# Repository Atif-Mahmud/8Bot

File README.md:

<h1 align="center">
    <br>
    
    <br>
    8Bot
    <br>
</h1>

<h4 align="center">Autonomous Pool Robot using Computer Vision</h4>

<h5 align="center">By: Atif Mahmud and Ethan Guo</h5>

<p align="center">

</p>

<p align="center">
    <a href="#procedures">Background and Motivation</a> •
    <a href="#procedures">Procedures</a> •
    <a href="#related-works">Related Works</a> •
    <a href="#learning-goals">Learning Goals</a> •
    <a href="#engineering-goals">Engineering Goals</a> •
    <a href="#license">License</a>
</p>

# Background and Motivation

# Procedures
## Dependencies
### Python Libraries
The projects primary language is python. Input parsing, computer vision, and
pathfinding are executed by python clients. The
[OpenCV-Python](https://docs.opencv.org/3.4.3/index.html) wrapper is used along
with [Numpy](http://www.numpy.org/) to do the various computer vision and
matrix operations this project employs.

#### Install Python-OpenCV
```shell
sudo apt-get install python-opencv
```

#### Install Pip
```shell
sudo apt-get install python-pip
```

#### Install Numpy
```shell
pip install numpy
```

### MQTT Broker
This project relies on low latency publisher/subscriber based data transfer. To
do this we employ MQTT. MQTT (Message Queuing Telemetry Transport) is an ISO
Standard messaging protocol commonly used in IOT applications. The one caveat
is that its publish/subscriber message pattern requires a persistent broker.
For the purposes of this project we employ the open source MQTT broker [Eclipse
Mosquitto](https://mosquitto.org).

#### Install Broker (Ubuntu)

(Ubuntu 12^)
```shell
sudo apt install mosquitto
```

(Older versions of Ubuntu)
```shell
sudo apt-add-repository ppa:mosquitto-dev/mosquitto-ppa
sudo apt-get update
```

#### Install Python MQTT Client Library
```shell
pip install paho-mqtt
```

# Learning Goals
- [ ] Continuous Integration
- [x] MQTT Protocol

# Engineering Goals
- [ ] Fast robot messaging infrastructure
- [ ] Robust object classification
- [ ] Robust environment description
- [ ] Robust localization

# Related Works

# License

GNU GENERAL PUBLIC LICENSE
Version 3, 29 June 2007

Refer to LICENSE.txt for full details

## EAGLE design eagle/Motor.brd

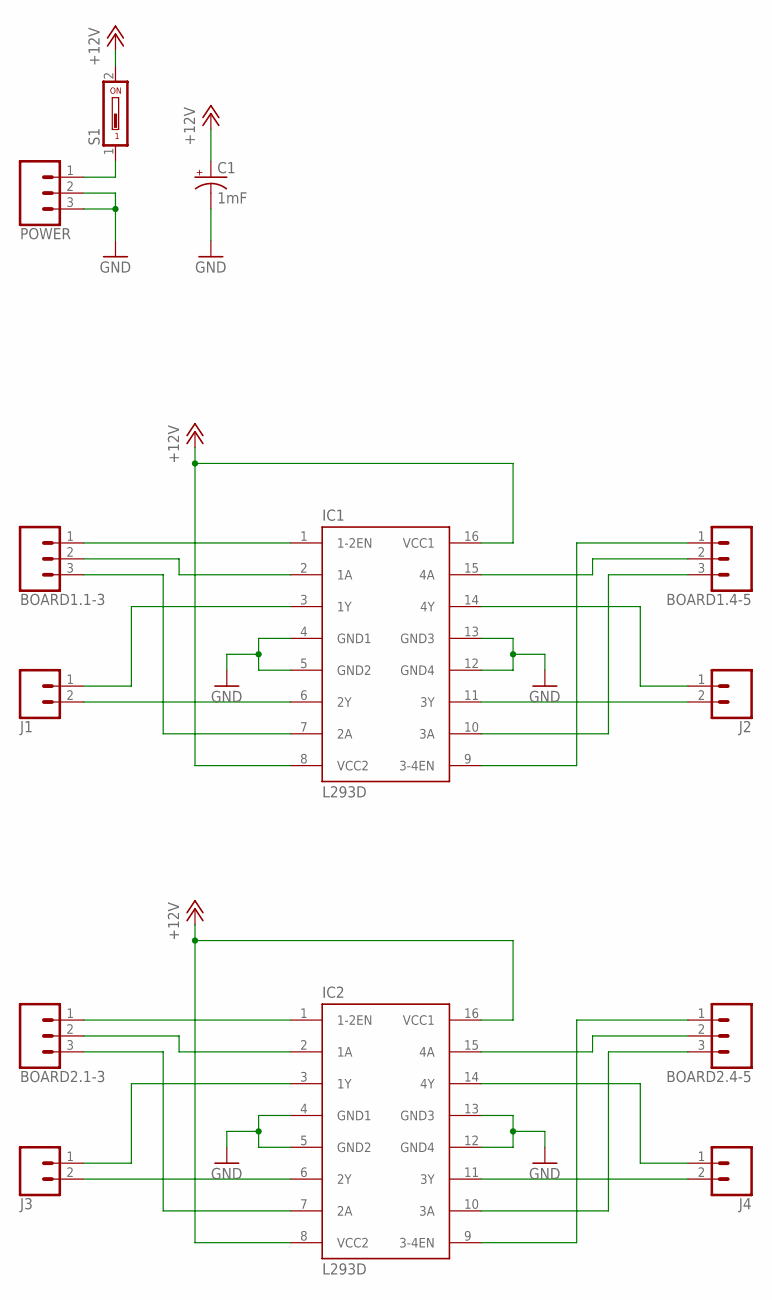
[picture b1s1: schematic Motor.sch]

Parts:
BOARD1.1-3, BOARD1.4-5, BOARD2.1-3, BOARD2.4-5: CONN_03; 1X03
C1: 1mF; CPOL-RADIAL-5MM-10MM
IC1, IC2: L293D; DIL16
J1, J2, J3, J4: CONN_02; 1X02
POWER: CONN_03; 1X03
S1: DS01; DS-01

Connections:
+9V: C1.+, IC1.8 (VCC2), IC1.16 (VCC1), IC2.8 (VCC2), IC2.16 (VCC1), S1.2
EN1: BOARD1.1-3.1, IC1.1 (1-2EN)
EN2: BOARD2.1-3.1, IC2.1 (1-2EN)
GND: C1.-, IC1.4 (GND1), IC1.5 (GND2), IC1.12 (GND4), IC1.13 (GND3), IC2.4 (GND1), IC2.5 (GND2), IC2.12 (GND4), IC2.13 (GND3), POWER.2, POWER.3
unnamed: IC1.3 (1Y), J1.1
unnamed: IC1.6 (2Y), J1.2
unnamed: IC1.14 (4Y), J2.1
unnamed: IC1.11 (3Y), J2.2
unnamed: BOARD1.1-3.2, IC1.2 (1A)
unnamed: BOARD1.1-3.3, IC1.7 (2A)
unnamed: BOARD1.4-5.3, IC1.10 (3A)
unnamed: BOARD1.4-5.2, IC1.15 (4A)
unnamed: IC2.3 (1Y), J3.1
unnamed: IC2.6 (2Y), J3.2
unnamed: IC2.14 (4Y), J4.1
unnamed: IC2.11 (3Y), J4.2
unnamed: BOARD2.1-3.2, IC2.2 (1A)
unnamed: BOARD2.1-3.3, IC2.7 (2A)
unnamed: BOARD2.4-5.1, IC2.9 (3-4EN)
unnamed: BOARD1.4-5.1, IC1.9 (3-4EN)
unnamed: BOARD2.4-5.3, IC2.10 (3A)
unnamed: BOARD2.4-5.2, IC2.15 (4A)
unnamed: POWER.1, S1.1

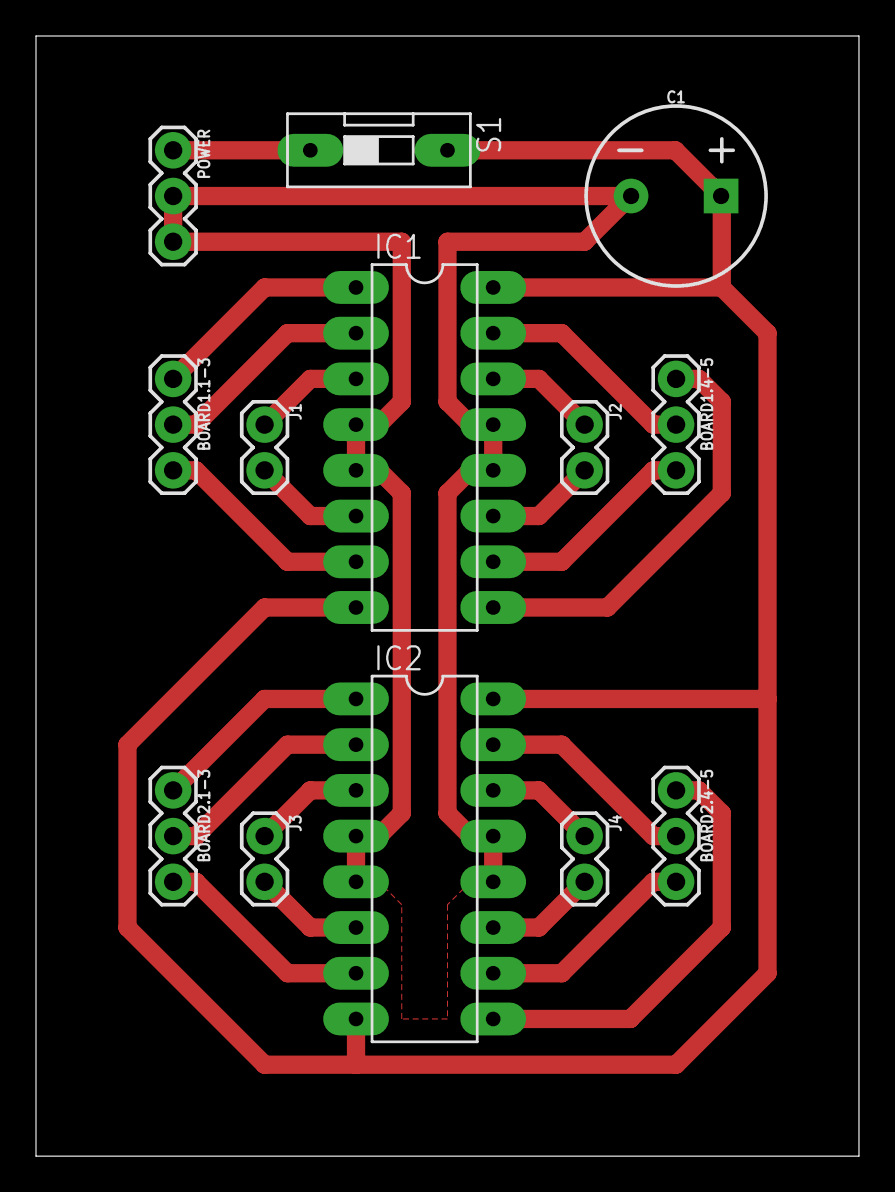
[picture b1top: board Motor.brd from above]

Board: 2 copper layers, 45.7 x 62.2 mm, 13 parts (0 on the bottom side), 23 nets.

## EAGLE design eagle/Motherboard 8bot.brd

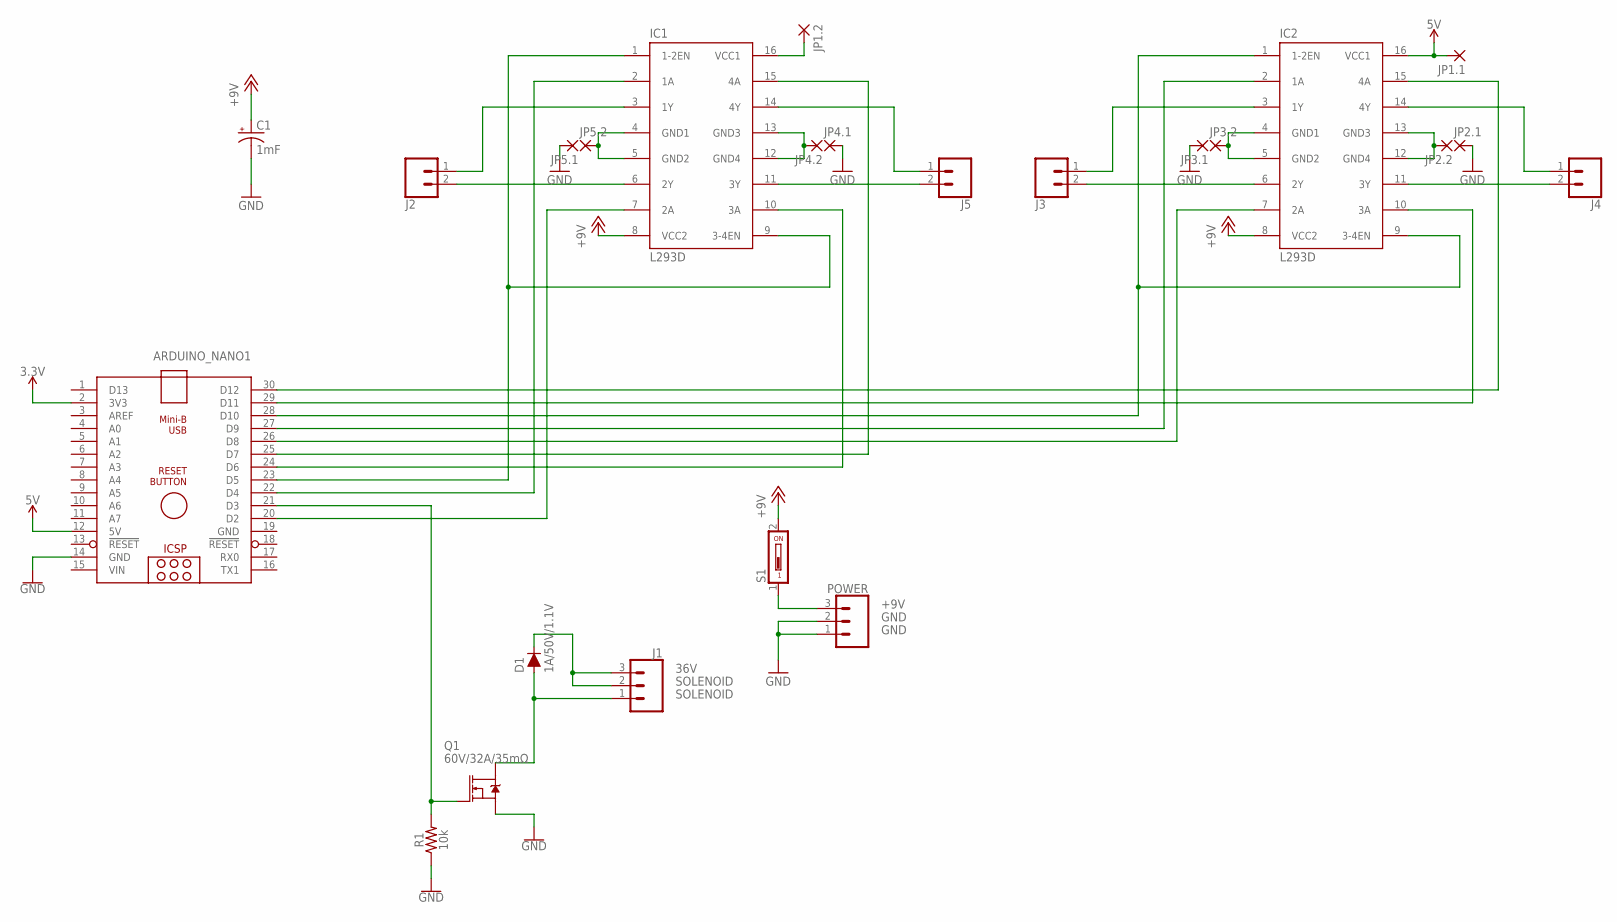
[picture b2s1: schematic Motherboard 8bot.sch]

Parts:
ARDUINO_NANO1: ARDUINO_NANO
C1: 1mF; CPOL-RADIAL-5MM-10MM
D1: 1A/50V/1.1V; DIODE-1N4001
IC1, IC2: L293D; DIL16
J1: CONN_03-SCREW-5MM; SCREWTERMINAL-5MM-3
J2, J3, J4, J5: CONN_02; 1X02
JP1.1, JP1.2, JP2.1, JP2.2, JP3.1, JP3.2, JP4.1, JP4.2, JP5.1, JP5.2: 1,6/0,8
POWER: CONN_03-SCREW-5MM; SCREWTERMINAL-5MM-3
Q1: 60V/32A/35mΩ; TO220V
R1: 10k; AXIAL-0.3
S1: DS01; DS-01

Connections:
3.3V: ARDUINO_NANO1.2 (3V3)
5V: ARDUINO_NANO1.12 (5V), IC2.16 (VCC1), JP1.1.1
36V: D1.C, J1.2, J1.3
+9V: C1.+, IC1.8 (VCC2), IC2.8 (VCC2), S1.2
EN1: ARDUINO_NANO1.23 (D5), IC1.1 (1-2EN), IC1.9 (3-4EN)
EN2: ARDUINO_NANO1.28 (D10), IC2.1 (1-2EN), IC2.9 (3-4EN)
GND: ARDUINO_NANO1.14 (GND), ARDUINO_NANO1.19 (GND), C1.-, JP2.1.1, JP3.1.1, JP4.1.1, JP5.1.1, POWER.1, POWER.2, Q1.3 (S), R1.P$1 (1)
unnamed: ARDUINO_NANO1.21 (D3), Q1.1 (G), R1.P$2 (2)
unnamed: IC1.3 (1Y), J2.1
unnamed: IC1.6 (2Y), J2.2
unnamed: IC1.14 (4Y), J5.1
unnamed: IC1.11 (3Y), J5.2
unnamed: ARDUINO_NANO1.20 (D2), IC1.7 (2A)
unnamed: ARDUINO_NANO1.22 (D4), IC1.2 (1A)
unnamed: ARDUINO_NANO1.24 (D6), IC1.10 (3A)
unnamed: IC2.3 (1Y), J3.1
unnamed: IC2.6 (2Y), J3.2
unnamed: IC2.14 (4Y), J4.1
unnamed: IC2.11 (3Y), J4.2
unnamed: IC1.16 (VCC1), JP1.2.1
unnamed: ARDUINO_NANO1.27 (D9), IC2.2 (1A)
unnamed: ARDUINO_NANO1.25 (D7), IC1.15 (4A)
unnamed: ARDUINO_NANO1.29 (D11), IC2.10 (3A)
unnamed: ARDUINO_NANO1.26 (D8), IC2.7 (2A)
unnamed: ARDUINO_NANO1.30 (D12), IC2.15 (4A)
unnamed: IC1.4 (GND1), IC1.5 (GND2), JP5.2.1
unnamed: POWER.3, S1.1
unnamed: IC1.12 (GND4), IC1.13 (GND3), JP4.2.1
unnamed: IC2.4 (GND1), IC2.5 (GND2), JP3.2.1
unnamed: IC2.12 (GND4), IC2.13 (GND3), JP2.2.1
SOLENOID: D1.A, J1.1, Q1.2 (D)
VIN: ARDUINO_NANO1.15 (VIN)

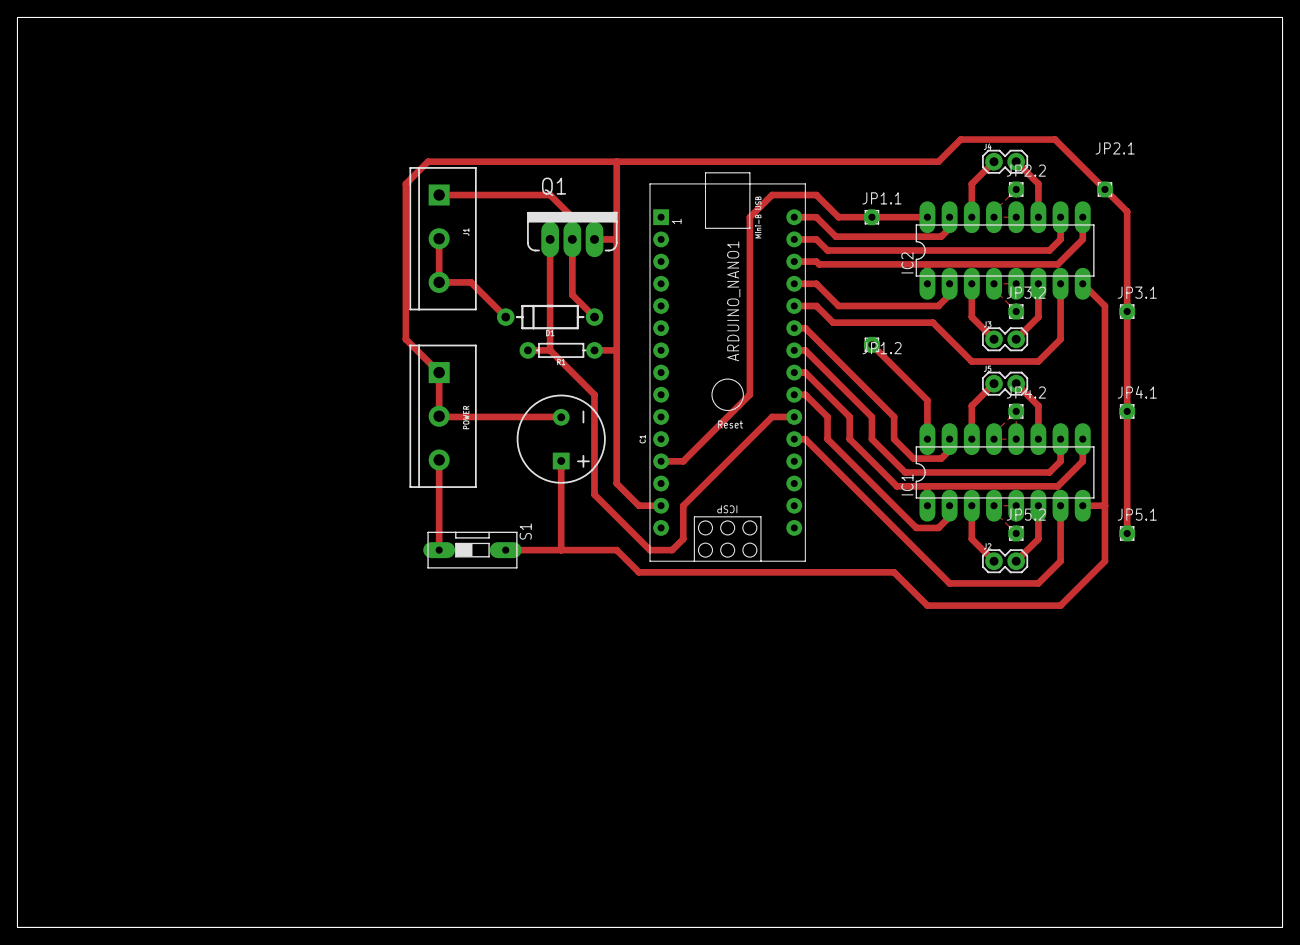
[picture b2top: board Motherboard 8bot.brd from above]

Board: 2 copper layers, 144.8 x 104.1 mm, 24 parts (0 on the bottom side), 30 nets.

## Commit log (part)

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2018-10-06 ✨ Add empty README file
2018-10-11 Make doc folder
2018-10-11 Compile proposal to pdf
2018-10-25 Add .gitignore
2018-10-25 Add bash script to initialize MQQT Broker
    References: #1
2018-10-25 ignore continuous integration temporarily
2018-10-25 Implement Master Controller general integration
    References: #4
2018-10-25 Implement Computer Vision integrations
    References: #2
2018-10-25 Remove debugging subscription
    Add error handling and logic to on_message()
    References: #4
2018-10-25 Add trivial ui integration
    References: #4
2018-10-30 Install packages
    References: #5
2018-10-30 Bootstrap Angular App with E2E testing
    References: #5
2018-11-01 Add continuous integration using .gitlab-ci.yml
    References: #5
2018-11-21 Design perspective transform class
    References #12
2018-11-21 Implement fourCorners method
    References: #12
2018-11-21 Add solenoid_test and (test) 8bot firmware
2018-11-21 Rename arduino/8bot/8bot.ino -> arduino/eightbot/eightbot.ino
2018-11-22 Create several ComputerVision utilities
    References #12
2018-11-22 Fixed taking commands, add debug stuff (LED and Serial echo)
2018-11-22 Implement calibrate class
    References: #13
2018-11-22 Rename cv_publisher.py to image_publisher.py
2018-11-22 Add keyboard_control.py
2018-11-22 Add debugging redundancies
2018-11-22 Computer Vision Demo V1
    References: #18
2018-11-22 Fix: Turn off DEBUG_ECHO Serial echo flag
2018-11-22 Improve calibration with contours
    References: #19
2018-11-22 Update MQTT publisher for CVNode
    References: #20
2019-09-24 Add gif to README.md
2019-11-01 Bump handlebars from 4.0.12 to 4.5.1 in /ui_node/eightbot
    Bumps [handlebars](https://github.com/wycats/handlebars.js) from 4.0.12 to 4.5.1.
    - [Release notes](https://github.com/wycats/handlebars.js/releases)
    - [Changelog](https://github.com/wycats/handlebars.js/blob/v4.5.1/release-notes.md)
    - [Commits](https://github.com/wycats/handlebars.js/compare/v4.0.12...v4.5.1)
2020-04-06 Bump acorn from 5.7.3 to 5.7.4 in /ui_node/eightbot
    Bumps [acorn](https://github.com/acornjs/acorn) from 5.7.3 to 5.7.4.
    - [Release notes](https://github.com/acornjs/acorn/releases)
    - [Commits](https://github.com/acornjs/acorn/compare/5.7.3...5.7.4)
2020-04-16 Bump https-proxy-agent from 2.2.1 to 2.2.4 in /ui_node/eightbot
    Bumps [https-proxy-agent](https://github.com/TooTallNate/node-https-proxy-agent) from 2.2.1 to 2.2.4.
    - [Release notes](https://github.com/TooTallNate/node-https-proxy-agent/releases)
    - [Commits](https://github.com/TooTallNate/node-https-proxy-agent/compare/2.2.1...2.2.4)
2020-07-31 Bump elliptic from 6.4.1 to 6.5.3 in /ui_node/eightbot
    Bumps [elliptic](https://github.com/indutny/elliptic) from 6.4.1 to 6.5.3.
    - [Release notes](https://github.com/indutny/elliptic/releases)
    - [Commits](https://github.com/indutny/elliptic/compare/v6.4.1...v6.5.3)
2020-09-04 Bump lodash.mergewith from 4.6.1 to 4.6.2 in /ui_node/eightbot
    Bumps [lodash.mergewith](https://github.com/lodash/lodash) from 4.6.1 to 4.6.2.
    - [Release notes](https://github.com/lodash/lodash/releases)
    - [Commits](https://github.com/lodash/lodash/commits)
2020-09-10 Bump http-proxy from 1.17.0 to 1.18.1 in /ui_node/eightbot
    Bumps [http-proxy](https://github.com/http-party/node-http-proxy) from 1.17.0 to 1.18.1.
    - [Release notes](https://github.com/http-party/node-http-proxy/releases)
    - [Changelog](https://github.com/http-party/node-http-proxy/blob/master/CHANGELOG.md)
    - [Commits](https://github.com/http-party/node-http-proxy/compare/1.17.0...1.18.1)
2020-12-11 Bump ini from 1.3.5 to 1.3.7 in /ui_node/eightbot
    Bumps [ini](https://github.com/isaacs/ini) from 1.3.5 to 1.3.7.
    - [Release notes](https://github.com/isaacs/ini/releases)
    - [Commits](https://github.com/isaacs/ini/compare/v1.3.5...v1.3.7)
2021-03-30 Bump y18n from 3.2.1 to 3.2.2 in /ui_node/eightbot
    Bumps [y18n](https://github.com/yargs/y18n) from 3.2.1 to 3.2.2.
    - [Release notes](https://github.com/yargs/y18n/releases)
    - [Changelog](https://github.com/yargs/y18n/blob/master/CHANGELOG.md)
    - [Commits](https://github.com/yargs/y18n/commits)
2021-05-08 Bump handlebars from 4.0.12 to 4.7.7 in /ui_node/eightbot
    Bumps [handlebars](https://github.com/wycats/handlebars.js) from 4.0.12 to 4.7.7.
    - [Release notes](https://github.com/wycats/handlebars.js/releases)
    - [Changelog](https://github.com/handlebars-lang/handlebars.js/blob/master/release-notes.md)
    - [Commits](https://github.com/wycats/handlebars.js/compare/v4.0.12...v4.7.7)
2021-05-11 Bump hosted-git-info from 2.7.1 to 2.8.9 in /ui_node/eightbot
    Bumps [hosted-git-info](https://github.com/npm/hosted-git-info) from 2.7.1 to 2.8.9.
    - [Release notes](https://github.com/npm/hosted-git-info/releases)
    - [Changelog](https://github.com/npm/hosted-git-info/blob/v2.8.9/CHANGELOG.md)
    - [Commits](https://github.com/npm/hosted-git-info/compare/v2.7.1...v2.8.9)
2021-05-27 Bump dns-packet from 1.3.1 to 1.3.4 in /ui_node/eightbot
    Bumps [dns-packet](https://github.com/mafintosh/dns-packet) from 1.3.1 to 1.3.4.
    - [Release notes](https://github.com/mafintosh/dns-packet/releases)
    - [Changelog](https://github.com/mafintosh/dns-packet/blob/master/CHANGELOG.md)
    - [Commits](https://github.com/mafintosh/dns-packet/compare/v1.3.1...v1.3.4)
2021-08-04 Bump tar from 2.2.1 to 2.2.2 in /ui_node/eightbot
    Bumps [tar](https://github.com/npm/node-tar) from 2.2.1 to 2.2.2.
    - [Release notes](https://github.com/npm/node-tar/releases)
    - [Changelog](https://github.com/npm/node-tar/blob/main/CHANGELOG.md)
    - [Commits](https://github.com/npm/node-tar/compare/v2.2.1...v2.2.2)
    ---
    updated-dependencies:
2021-09-29 Bump i from 0.3.6 to 0.3.7 in /ui_node/eightbot
    Bumps [i](https://github.com/pksunkara/inflect) from 0.3.6 to 0.3.7.
    - [Release notes](https://github.com/pksunkara/inflect/releases)
    - [Commits](https://github.com/pksunkara/inflect/compare/v0.3.6...v0.3.7)
    ---
    updated-dependencies:
    - dependency-name: i
2021-10-06 Bump url-parse from 1.4.3 to 1.5.3 in /ui_node/eightbot
    Bumps [url-parse](https://github.com/unshiftio/url-parse) from 1.4.3 to 1.5.3.
    - [Release notes](https://github.com/unshiftio/url-parse/releases)
    - [Commits](https://github.com/unshiftio/url-parse/compare/1.4.3...1.5.3)
    ---
    updated-dependencies:
    - dependency-name: url-parse
2022-01-15 Bump shelljs from 0.8.2 to 0.8.5 in /ui_node/eightbot
    Bumps [shelljs](https://github.com/shelljs/shelljs) from 0.8.2 to 0.8.5.
    - [Release notes](https://github.com/shelljs/shelljs/releases)
    - [Changelog](https://github.com/shelljs/shelljs/blob/master/CHANGELOG.md)
    - [Commits](https://github.com/shelljs/shelljs/compare/v0.8.2...v0.8.5)
    ---
    updated-dependencies:
2022-02-11 Bump karma from 3.0.0 to 6.3.14 in /ui_node/eightbot
    Bumps [karma](https://github.com/karma-runner/karma) from 3.0.0 to 6.3.14.
    - [Release notes](https://github.com/karma-runner/karma/releases)
    - [Changelog](https://github.com/karma-runner/karma/blob/master/CHANGELOG.md)
    - [Commits](https://github.com/karma-runner/karma/compare/v3.0.0...v6.3.14)
    ---
    updated-dependencies:
2022-02-18 Bump url-parse from 1.4.3 to 1.5.7 in /ui_node/eightbot
    Bumps [url-parse](https://github.com/unshiftio/url-parse) from 1.4.3 to 1.5.7.
    - [Release notes](https://github.com/unshiftio/url-parse/releases)
    - [Commits](https://github.com/unshiftio/url-parse/compare/1.4.3...1.5.7)
    ---
    updated-dependencies:
    - dependency-name: url-parse
2022-02-26 Bump url-parse from 1.4.3 to 1.5.10 in /ui_node/eightbot
    Bumps [url-parse](https://github.com/unshiftio/url-parse) from 1.4.3 to 1.5.10.
    - [Release notes](https://github.com/unshiftio/url-parse/releases)
    - [Commits](https://github.com/unshiftio/url-parse/compare/1.4.3...1.5.10)
    ---
    updated-dependencies:
    - dependency-name: url-parse
2022-06-02 Bump @angular/core from 7.0.1 to 11.0.5 in /ui_node/eightbot
    Bumps [@angular/core](https://github.com/angular/angular/tree/HEAD/packages/core) from 7.0.1 to 11.0.5.
    - [Release notes](https://github.com/angular/angular/releases)
    - [Changelog](https://github.com/angular/angular/blob/main/CHANGELOG.md)
    - [Commits](https://github.com/angular/angular/commits/11.0.5/packages/core)
    ---
    updated-dependencies:
2022-09-08 Bump jszip from 3.1.5 to 3.10.1 in /ui_node/eightbot
    Bumps [jszip](https://github.com/Stuk/jszip) from 3.1.5 to 3.10.1.
    - [Release notes](https://github.com/Stuk/jszip/releases)
    - [Changelog](https://github.com/Stuk/jszip/blob/main/CHANGES.md)
    - [Commits](https://github.com/Stuk/jszip/compare/v3.1.5...v3.10.1)
    ---
    updated-dependencies:
2022-11-11 Bump socket.io-parser and karma in /ui_node/eightbot
    Bumps [socket.io-parser](https://github.com/socketio/socket.io-parser) to 4.2.1 and updates ancestor dependency [karma](https://github.com/karma-runner/karma). These dependencies need to be updated t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
    Updates `socket.io-parser` from 3.2.0 to 4.2.1
    - [Release notes](https://github.com/socketio/socket.io-parser/releases)
    - [Changelog](https://github.com/socketio/socket.io-parser/blob/main/CHANGELOG.md)
    - [Commits](https://github.com/socketio/socket.io-parser/compare/3.2.0...4.2.1)
    Updates `karma` from 3.0.0 to 6.4.1
2022-11-17 Bump loader-utils and @angular-devkit/build-angular in /ui_node/eightbot
    Bumps [loader-utils](https://github.com/webpack/loader-utils) to 3.2.1 and updates ancestor dependency [@angular-devkit/build-angular](https://github.com/angular/angular-cli). These dependencies need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
    Updates `loader-utils` from 1.1.0 to 3.2.1
    - [Release notes](https://github.com/webpack/loader-utils/releases)
    - [Changelog](https://github.com/webpack/loader-utils/blob/master/CHANGELOG.md)
    - [Commits](https://github.com/webpack/loader-utils/compare/v1.1.0...v3.2.1)
    Updates `@angular-devkit/build-angular` from 0.10.3 to 15.0.0
2022-12-04 Bump decode-uri-component from 0.2.0 to 0.2.2 in /ui_node/eightbot
    Bumps [decode-uri-component](https://github.com/SamVerschueren/decode-uri-component) from 0.2.0 to 0.2.2.
    - [Release notes](https://github.com/SamVerschueren/decode-uri-component/releases)
    - [Commits](https://github.com/SamVerschueren/decode-uri-component/compare/v0.2.0...v0.2.2)
    ---
    updated-dependencies:
    - dependency-name: decode-uri-component
2022-12-09 Bump qs, express and body-parser in /ui_node/eightbot
    Bumps [qs](https://github.com/ljharb/qs), [express](https://github.com/expressjs/express) and [body-parser](https://github.com/expressjs/body-parser). These dependencies needed to be updated together.
    Updates `qs` from 6.5.2 to 6.5.3
    - [Release notes](https://github.com/ljharb/qs/releases)
    - [Changelog](https://github.com/ljharb/qs/blob/main/CHANGELOG.md)
    - [Commits](https://github.com/ljharb/qs/compare/v6.5.2...v6.5.3)
    Updates `express` from 4.16.4 to 4.18.2
2022-12-31 Bump json5 and @angular-devkit/build-angular in /ui_node/eightbot
    Bumps [json5](https://github.com/json5/json5) to 2.2.2 and updates ancestor dependency [@angular-devkit/build-angular](https://github.com/angular/angular-cli). These dependencies need to be updated t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
    Updates `json5` from 0.5.1 to 2.2.2
    - [Release notes](https://github.com/json5/json5/releases)
    - [Changelog](https://github.com/json5/json5/blob/main/CHANGELOG.md)
    - [Commits](https://github.com/json5/json5/compare/v0.5.1...v2.2.2)
    Updates `@angular-devkit/build-angular` from 0.10.3 to 15.0.4

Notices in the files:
parts and their libraries:
SparkFun-Connectors: Licensing: Creative Commons ShareAlike 4.0 International - https://creativecommons.org/licenses/by-sa/4.0
